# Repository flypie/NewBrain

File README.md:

# NewBrain
Newbury/Grundy NewBrain schematics

Creating a KiCAD schematic for the NewBrain and hopefully progressing on to a buildable version with COP420 replaced.

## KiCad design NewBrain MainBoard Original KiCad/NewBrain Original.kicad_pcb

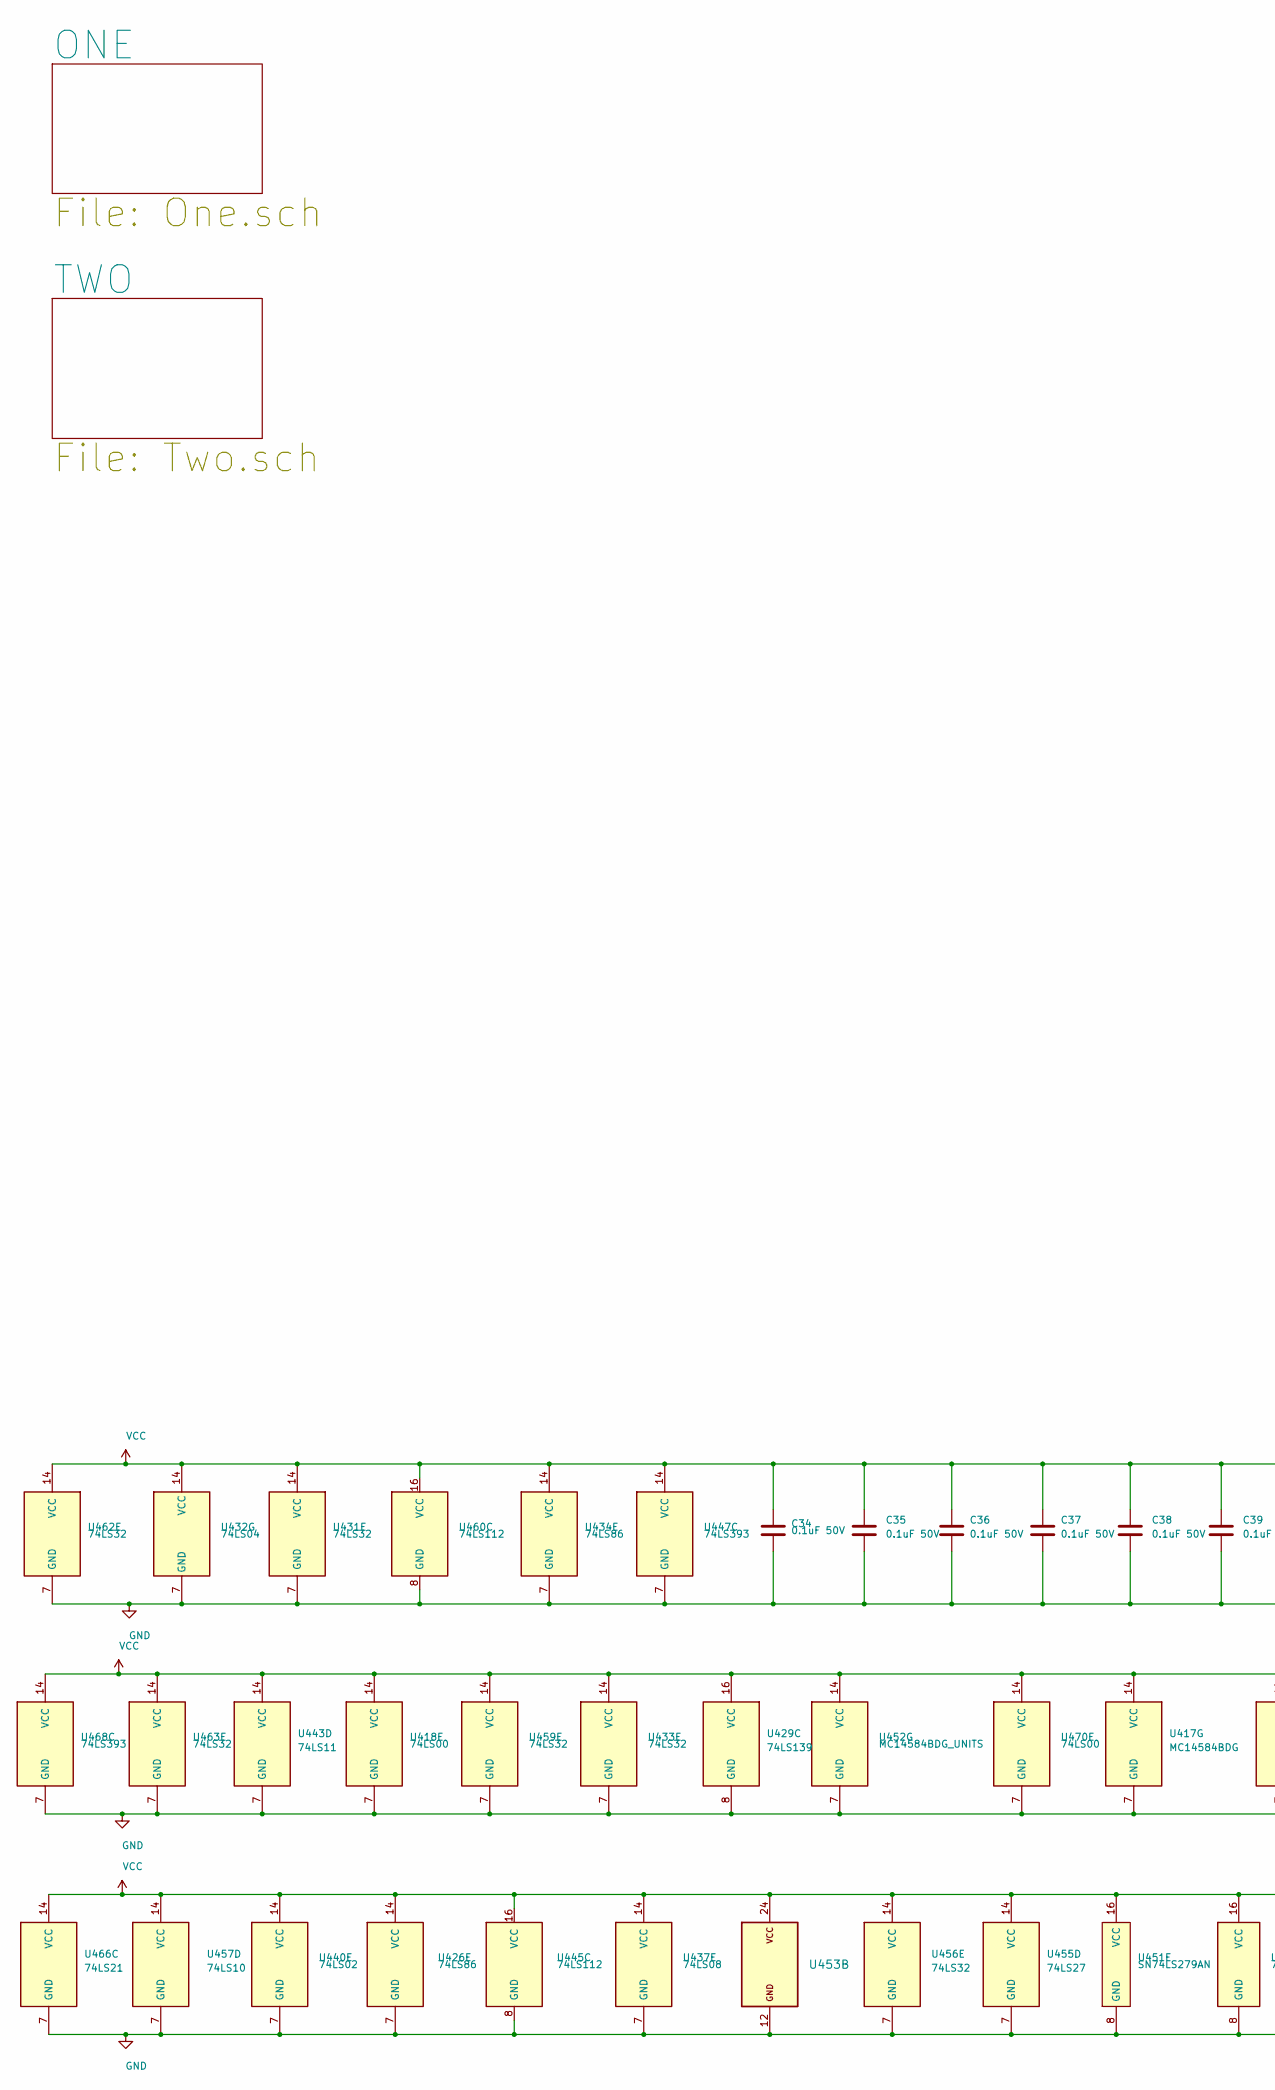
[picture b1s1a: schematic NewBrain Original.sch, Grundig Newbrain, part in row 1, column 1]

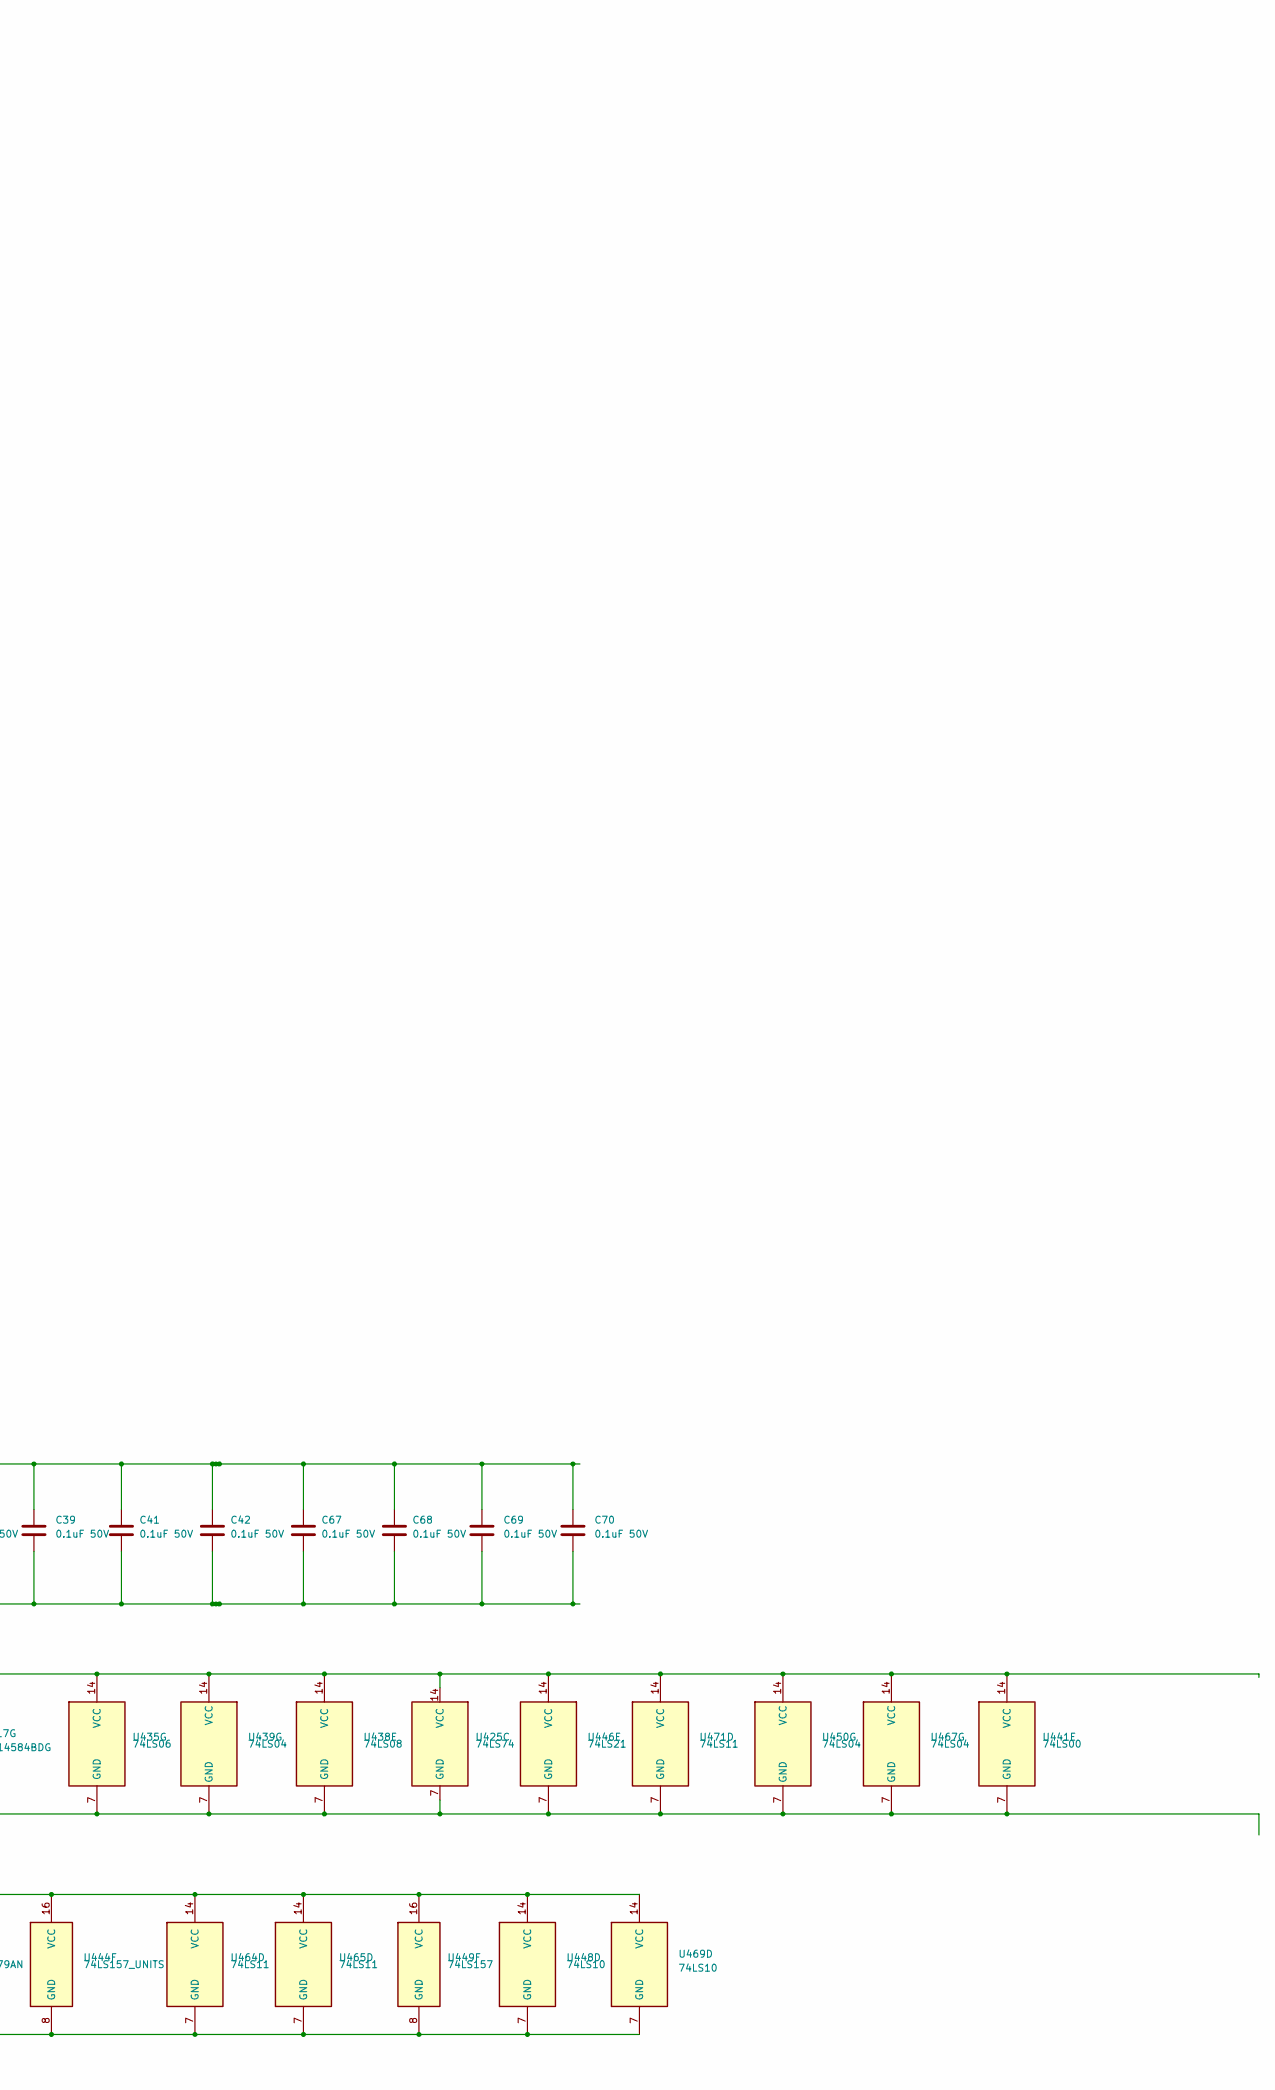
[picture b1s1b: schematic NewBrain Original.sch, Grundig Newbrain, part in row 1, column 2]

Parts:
C34, C35, C36, C37, C38, C39, C41, C42, C67, C68, C69, C70: 0.1uF 50V; C_Axial_L3.8mm_D2.6mm_P7.50mm_Horizontal
U417: MC14584BDG; DIP-14_W7.62mm
U418, U441, U470: 74LS00; DIP-14_W7.62mm
U425: 74LS74; DIP-14_W7.62mm
U426, U434: 74LS86; DIP-14_W7.62mm
U429: 74LS139; DIP-16_W7.62mm
U431, U433, U456, U459, U462, U463: 74LS32; DIP-14_W7.62mm
U432, U439, U450, U467: 74LS04; DIP-14_W7.62mm
U435: 74LS06; DIP-14_W7.62mm
U437, U438: 74LS08; DIP-14_W7.62mm
U440: 74LS02; DIP-14_W7.62mm
U443, U464, U465, U471: 74LS11; DIP-14_W7.62mm
U444: 74LS157_UNITS; DIP-16_W7.62mm
U445, U460: 74LS112; DIP-16_W7.62mm
U446, U466: 74LS21; DIP-14_W7.62mm
U447, U468: 74LS393; DIP-14_W7.62mm
U448, U457, U469: 74LS10; DIP-14_W7.62mm
U449: 74LS157; DIP-16_W7.62mm
U451: SN74LS279AN; DIP-16_W7.62mm; Mouser Part Number 595-SN74LS279AN
U452: MC14584BDG_UNITS; DIP-14_W7.62mm
U453: 2716-Memory_EPROM; DIP-24_W10.16mm_LongPads
U455: 74LS27; DIP-14_W7.62mm

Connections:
K12: C34.2, C35.2, C36.2, C37.2, C38.2, C39.2, C41.2, C42.2, C67.2, C68.2, C69.2, C70.2, U417.7 (GND), U418.7 (GND), U425.7 (GND), U426.7 (GND), U429.8 (GND), U431.7 (GND), U432.7 (GND), U433.7 (GND), U434.7 (GND), U435.7 (GND), U437.7 (GND), U438.7 (GND), U439.7 (GND), U440.7 (GND), U441.7 (GND), U443.7 (GND), U444.8 (GND), U445.8 (GND), U446.7 (GND), U447.7 (GND), U448.7 (GND), U449.8 (GND), U450.7 (GND), U451.8 (GND), U452.7 (GND), U453.12 (GND), U455.7 (GND), U456.7 (GND), U457.7 (GND), U459.7 (GND), U460.8 (GND), U462.7 (GND), U463.7 (GND), U464.7 (GND), U465.7 (GND), U466.7 (GND), U467.7 (GND), U468.7 (GND), U469.7 (GND), U470.7 (GND), U471.7 (GND); also elsewhere on the board
VCC: C34.1, C35.1, C36.1, C37.1, C38.1, C39.1, C41.1, C42.1, C67.1, C68.1, C69.1, C70.1, U417.14 (VCC), U418.14 (VCC), U425.14 (VCC), U426.14 (VCC), U429.16 (VCC), U431.14 (VCC), U432.14 (VCC), U433.14 (VCC), U434.14 (VCC), U435.14 (VCC), U437.14 (VCC), U438.14 (VCC), U439.14 (VCC), U440.14 (VCC), U441.14 (VCC), U443.14 (VCC), U444.16 (VCC), U445.16 (VCC), U446.14 (VCC), U447.14 (VCC), U448.14 (VCC), U449.16 (VCC), U450.14 (VCC), U451.16 (VCC), U452.14 (VCC), U453.24 (VCC), U455.14 (VCC), U456.14 (VCC), U457.14 (VCC), U459.14 (VCC), U460.16 (VCC), U462.14 (VCC), U463.14 (VCC), U464.14 (VCC), U465.14 (VCC), U466.14 (VCC), U467.14 (VCC), U468.14 (VCC), U469.14 (VCC), U470.14 (VCC), U471.14 (VCC); also elsewhere on the board

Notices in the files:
NewBrain MainBoard Original KiCad/NewBrain Original.sch:
Copyright John Bradley 2020
